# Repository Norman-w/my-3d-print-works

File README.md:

# 我的 3D 打印作品

收集自己设计、打印和验证过的 3D 打印作品。这里是后续 3D 打印模型、打印文件、预览图和说明的维护入口；原仓库保留作历史来源。

## 作品总索引

| 类别 | 项目与用途 | 项目 README | 缩略图 | 原仓库 |
|---|---|---|---|---|
| 卫浴 | 洗手盆下水管转接件：连接两种外丝、带连续过渡和梅花握持纹 | [打开](works/bathroom/sink-drain-adapter/README.md) |  | — |
| 光学 / 收纳 | 角膜塑形镜清洁套装盒：铰链、锁扣和清洁收纳结构 | [打开](works/optics/orthokeratology-lens-cleaning-kit-box/README.md) |  | [原仓库](https://github.com/Norman-w/OrthokeratologyLensCleaningKitBox) |
| 健康 / 设备保护 | 理疗仪线缆串联保护盒：保护控制板、线缆出线和散热区域 | [打开](works/health/therapy-cable-inline-box/README.md) |  | [原仓库](https://github.com/Norman-w/therapy-cable-inline-box-for-physio) |

> 收录标准：优先收录体量较小、生活中直接使用、以 3D 打印件为主体的作品。大型体育设备、复杂机构、电路和完整业务工程保留在原仓库，不进入这里。智能拖挂房车项目也保持在原仓库。

## 目录

```text
works/<作品名>/      作品源文件、打印文件、预览和验证记录
templates/work/     新作品模板
scripts/             工具脚本
```

每个作品至少记录：用途、尺寸、配套实物、`.scad` 源文件、STL / 3MF、预览图、验证结果、打印参数和未完成项。

## 状态

`concept` → `digital-verified` → `sliced` → `printed` → `assembled` → `accepted`

数字模型通过、切片成功或网页预览，都不等于实物装配验收。

## 新建作品

```sh
sh scripts/new-work.sh my-object
```

纯链接版索引：[`works/catalog.md`](works/catalog.md)

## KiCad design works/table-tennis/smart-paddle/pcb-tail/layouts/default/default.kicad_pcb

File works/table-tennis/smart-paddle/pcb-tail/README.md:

# SmartPaddle 尾部线路板（`pcb-tail`）

> 当前 **M7.C5** 组合的独立满截面尾板，与 `pcb/` 主板分开维护；充电、USB、按键和 LED 均在本板。版本只记录在说明与 KiCad 标题栏，工程、PCB、同步脚本和交接文件使用跨版本通用名称。

> **当前设计与旧板安全状态（2026-08-23）：** 当前 M7.C5 尾板为 33 个封装、502 段走线、53 个过孔和双面 GND 覆铜；KiCad DRC 为 0 error / 0 unconnected，保留 3 条已审计 warning。J1 16触点、J4/SW1、电源拓扑、主尾板线序与 M7 机械干涉门禁均通过，整机 release gate 已通过。当前达到独立工程样板下单标准；下单前仍须人工确认 Gerber/钻孔、板厚、铜厚、表面处理和颜色。所有按旧 J1 错误映射制造或已焊接的尾板及旧制造文件仍不得上电、插 USB 或再次下单。
>
> `layouts/default/export-preview/` 中除重新生成的 `fp-usb16p-selfcheck.png` 外，其余图像是本次审计前的历史预览，不是当前 J1 或制造状态的证据。

## 方向约定

| 面 | 朝向 |
|---|---|
| 正面 `F.Cu` | 拍柄末端（世界 −Y） |
| 背面 `B.Cu` | 拍头（世界 +Y） |

- `KiCad X` = 柄 `X`
- `KiCad Y` = 柄 `Z`
- 板厚沿世界 `Y`（1.0 mm）

## 专用电池接口（已放置、已布线）

- 板端：JST ACH `BM02B-ACHSS-GAN-ETF`，1.20 mm、2P、SMT 顶插；配套线端 `ACHR-02V-S` + `SACH-003G-P0.2`，成品线固定为 AWG28。
- J4 footprint：`Connector_JST:JST_ACH_BM02B-ACHSS-GAN-ETF_1x02-1MP_P1.20mm_Vertical`。电气定义固定为 **Pin 1=`BAT_P`/red**、**Pin 2=`GND`/black**；它与现有 `J2.3 BAT_P` / `J2.2 GND` 并联，电池不得接主板 `SYS_5V_IN`。
- J4 位于 B.Cu `(-2.794,-7.000) mm`、90°；Pad 1 全局 `(-0.919,-6.400) mm`，Pad 2 `(-0.919,-7.600) mm`，两个 `MP` 固定焊盘均 NC。它只沿 KiCad Y 平移 1.031 mm，为插合后的 J2 线端留出净空；当前两脚已完成布线并通过 DRC。
- 选型、采购词、电流门禁和官方资料见 [`../docs/battery-connector-jst-ach-2p/README.md`](../docs/battery-connector-jst-ach-2p/README.md)。旧 PH 方案已明确停用；官方 XH 2.50 与市售“XH2.54”不能凭名称保证互配。

## 用户按键（已换 footprint、已布线；针孔可用，推杆可选）

- SW1 已由 4.5×4.5 mm THT 换成 Omron `B3U-1000P` SMD，footprint 为 `Button_Switch_SMD:SW_SPST_B3U-1000P`；保持原锚点 `(-1.651,-5.461) mm` 和 `-90°`，没有移动或旋转其他器件。
- Pad 1=`user_btn`、Pad 2=`GND`，当前已布线并接入双面 GND 覆铜。
- 拍柄基准操作方式为 SW1 中心 Ø2.0 mm 直通针孔，可用针尖/笔尖操作，不用固定柱长期压住开关。另有从壳内装入、Ø3.0 mm 法兰防外脱的 Ø1.6 mm 可选活动推杆；推杆批量使用前仍须做行程试片。详见 [`../docs/tail-user-switch-b3u-1000p/README.md`](../docs/tail-user-switch-b3u-1000p/README.md) 和 [`../docs/tail-handle-interference/README.md`](../docs/tail-handle-interference/README.md)。当前四层制造 STL 和两张 `paddle_m7_*` 打印拼板已按正式尾板干涉事实重新生成。
- `python3 pcb-tail/scripts/audit_battery_connector_j4.py --allow-copper` 同时核对 J4 与 SW1 的位姿、针脚网络和项目内资料；铜完整性由尾板独立制造门禁另行检查。

## 主板线束接口（卧插、已布线）

- J2/J3 均为 Molex PicoBlade `53261-0471`、1.25 mm、4P、卧插 SMT；与原 53398 立插使用同一 `51021-0400` 4P 线端体系，但两种板端 footprint 不能互换。
- J2 位于 B.Cu `(-11.300,-0.600) mm`、−90°；J3 位于 B.Cu `(+6.300,-5.800) mm`、180°。两只插口均朝板内侧，线束平行 PCB 离开；逐脚网络仍以 [`ADAPTER_HARNESS.md`](ADAPTER_HARNESS.md) 为准。
- 最终紧凑布局已经由 `audit_power_architecture.py` 锁定：C1/C2 两颗同值 100 nF 分别就近服务 D1 与 U1，U3/L1/C3/C4/C6 构成已审计的本地功率岛。J2/J3/J4 的完整插合包络已写入机械干涉事实并由壳体导出链消费。
- 原厂证据、封装快照、Pin 1 方向及机械说明见 [`../docs/molex-picoblade-53261-4p-horizontal/README.md`](../docs/molex-picoblade-53261-4p-horizontal/README.md)。

## 打开

```text
pcb-tail/layouts/default/default.kicad_pro
```

## 工作流

当前尾板是已布线生产基线。J1 封装仍可重复生成和逐触点检查：

```bash
python3 pcb-tail/scripts/gen_usb_16p_vert_smt_fp.py
python3 pcb-tail/scripts/audit_usb_16p_j1.py
python3 pcb-tail/scripts/audit_battery_connector_j4.py
```

Atopile 只构建到 `layouts/staging/`；必须连续构建两次，再用项目同步脚本安全带入当前板。不得直接让 Atopile 覆盖 `layouts/default/`，`ato build` 的成功退出也不能替代逐触点审计：

```bash
cd pcb-tail
ato build
ato build
cd ..
/Applications/KiCad/KiCad.app/Contents/Frameworks/Python.framework/Versions/3.9/bin/python3 \
  pcb-tail/scripts/sync_power_architecture.py
/Applications/KiCad/KiCad.app/Contents/Frameworks/Python.framework/Versions/3.9/bin/python3 \
  pcb-tail/scripts/place_power_architecture.py
python3 scripts/validate_power_rework.py --release-gate --target tail
```

入口：`main.ato:SmartPaddleTail`（`ato.yaml`）。

外形：`web/src/data/userBezierProfiles.json` + `enclosure/parameters.scad`  
内缩：`wall_t + tail_cavity_inset`；`board_clearance = -0.50` 嵌入环槽。

壳体开孔：`./scripts/export-stl.sh`（含 Step6，按本板位姿干涉，并生成独立 B3U 活动推杆）；当前 M7.C5 已按正式尾板重新生成 `paddle_m7_*` 四层件和两张打印拼板。

## 文件

| 文件 | 说明 |
|------|------|
| `main.ato` | atopile 入口 |
| `layouts/default/default.kicad_pro` | 工程 |
| `generate_outline.py` | 从尾端截面生成 Edge.Cuts |
| `tail-outline-preview.svg` / `.png` | 2D 预览 |
| `geometry-report.txt` / `outline-facts.json` | 尺寸事实 |
| `ADAPTER_HARNESS.md` | 当前主板与本尾板的 4P→5P 转接、装配及验证 |
| `harness/adapter.json` | 由两块实际 PCB 焊盘网络校验的线束真理源 |

> 注意：本尾板为 2×4P，当前主板栈道为正反 2×5P，不能直接插接。
> 使用上述转接线束；主板的 UART TX/RX 保留为独立调试口。

## 已知瑕疵

- 当前 KiCad 3D Viewer 及导出的 3D 预览中，部分器件模型的比例/尺度与实物不一致；这只影响 3D 外观预览，不代表 PCB 焊盘、板框或器件采购尺寸发生变化。
- 3D 模型比例问题本身不用于判断焊盘；但这条说明不适用于 J1 或 J2/J3。J1 已按 H=5.8 短脚主数据表逐触点纠正；J2/J3 使用 KiCad 9 stock 53261 footprint/STEP，并另按 Molex 销售图审计 land 与 3.40 mm 配合高度。
- 下一版装配图或下单前，仍应按供应商机械图和首件实物重新检查 Type-C、卧插线束的弯曲半径、按键孔和打印公差。

## 嘉立创实验样板资料

> 已运行两板独立门禁并生成新的工程样板包；旧包仍禁止使用。尾板当前为 0 DRC error / 0 unconnected，Ø2.0 mm 针孔是独立可用的按键基准，可选推杆的试片状态不会掩盖电气验收。两板独立上传包位于 `fab/jlcpcb-orders/20260823-m7c5/`。

从仓库根目录运行：

```sh
# 仅尾板
python3 pcb/scripts/export_order_packages.py --target tail

# 主板、尾板分别形成两个独立订单包
python3 pcb/scripts/export_order_packages.py --target separate
```

当前尾板工程样板包位于 `pcb-tail/output/fab/20260817-tail-m7c5/`（本地制造输出，不纳入 Git），其中上传 ZIP 与审阅 ZIP 分离。尾板为 2 层、板厚 1.00 mm；下单页仍须人工冻结铜厚、表面处理及颜色。建议首板使用 1 oz 铜、沉金、绿色阻焊；若改用其他工艺应记录订单参数。该放行只覆盖尾板工程样板，不等于主板、整机或量产放行。

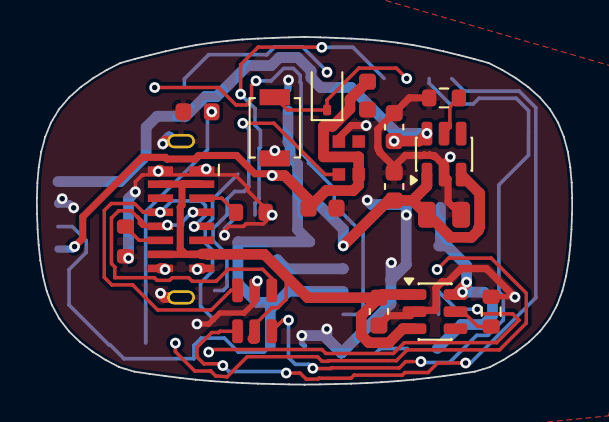
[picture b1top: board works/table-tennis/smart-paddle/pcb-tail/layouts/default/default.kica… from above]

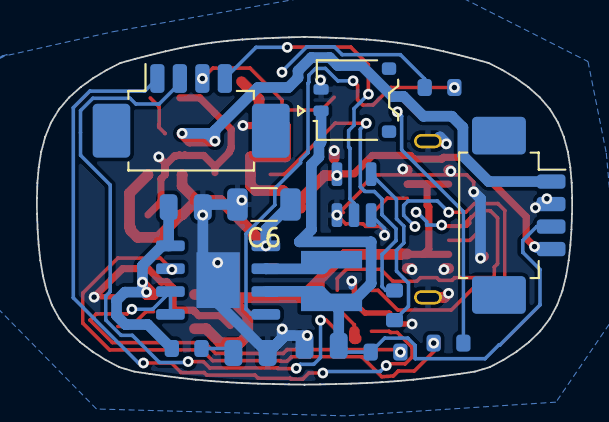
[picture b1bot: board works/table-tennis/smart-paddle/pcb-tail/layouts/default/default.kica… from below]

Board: 2 copper layers, 29.7 x 19.3 mm, 33 parts (15 on the bottom side), 26 nets.

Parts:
C1, C2: 100nF; C_0603_1608Metric
C3, C4, C5, C7: 10uF 10V X5R/X7R; C_0805_2012Metric
C6: 22uF 10V X5R/X7R; C_1206_3216Metric
C8, C9, C10: 100nF 10V X7R; C_0603_1608Metric
D1: WS2812B-2020; LED_WS2812B-2020_PLCC4_2.0x2.0mm
D2: 1N4148W; D_SOD-323
J1: USB-C-16P-VERTICAL-H5.8-SHORT; USB_C_Receptacle_16P_Vertical_SMT_Short
J2, J3: Molex 53261-0471; Molex_PicoBlade_53261-0471_1x04-1MP_P1.25mm_Horizontal
J4: BM02B-ACHSS-GAN-ETF; JST_ACH_BM02B-ACHSS-GAN-ETF_1x02-1MP_P1.20mm_Vertical
L1: XFL4020-222MEC 2.2uH; L_Coilcraft_XxL4020
LED1: LTST-C190KGKT; LED_0603_1608Metric
R1, R2: 5.1k 1%; R_0603_1608Metric
R3: 330R; R_0603_1608Metric
R4: 10k; R_0603_1608Metric
R5: 200R; R_0603_1608Metric
R6: 1k; R_0603_1608Metric
R7: 2R; R_0603_1608Metric
R8: 43.2k 1%; R_0603_1608Metric
R9: 59k 1%; R_0603_1608Metric
SW1: B3U-1000P; SW_SPST_B3U-1000P
U1: SN74AHCT1G125DBVR; SOT-23-5
U2: USBLC6-2SC6; SOT-23-6
U3: IP5305T; IP5305T_HSOP-8-1EP
U4, U5: TPS2553DBVR; SOT-23-6

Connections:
GND: C1.2, C2.2, C3.2, C4.2, C5.2, C6.2, C7.2, C8.2, C9.2, C10.2, D1.2, J1.A1, J1.A12, J1.B1, J1.B12, J1.S1, J2.2, J4.2, LED1.1, R1.2, R2.2, R8.2, R9.2, SW1.2, U1.1, U1.3, U2.2, U3.9, U4.2, U5.2
bat_p: C3.1, J2.3, J4.1, L1.2, R6.2, U3.6
cc1: J1.A5, R1.1
cc2: J1.B5, R2.1
led_ahct_y: R3.1, U1.4
led_data: J3.4, U1.2
led_din: D1.3, R3.2
led_stat_a: LED1.2, R5.2
pmic_key: R4.1, U3.5
pmic_key_isolated: D2.2, R4.2
pmic_led1: R5.1, U3.2
pmic_led23: R6.1, U3.3, U3.4
sw_node: L1.1, U3.7
system_ilim: R8.1, U4.5
usb_dn: J3.1, U2.4
usb_dn_conn: J1.A7, J1.B7, U2.3
usb_dp: J3.2, U2.6
usb_dp_conn: J1.A6, J1.B6, U2.1
user_btn: D2.1, J3.3, SW1.1
v5_sw_return: C1.1, C2.1, D1.4, J2.4, U1.5
vbus: C10.1, J1.A4, J1.A9, J1.B4, J1.B9, U2.5, U5.1, U5.3
vbus_ilim: R9.1, U5.5
vbus_limited: C4.1, R7.1, U3.1, U5.6
vin_damp_mid: C5.1, R7.2
vout_5v: C9.1, J2.1, U4.6
vout_5v_raw: C6.1, C7.1, C8.1, U3.8, U4.1, U4.3

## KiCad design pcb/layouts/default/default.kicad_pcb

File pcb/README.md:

# SmartPaddle 主板

> **当前仓库状态（2026-08-23）：** 当前硬件组合为 **M7.C5**。`layouts/default/default.kicad_pcb` 标题栏为 `SmartPaddle Main PCB / C5`。当前工作区主板为 **67 封装、1062 段线、142 个过孔、1 个 GND 铜区**（另有 MCU 天线双面规则区），KiCad 9.0.6 DRC 为 **0 error / 0 warning / 0 未连接**，`scripts/validate_power_rework.py --release-gate --target all` 已通过。当前板已达到**工程样板下单**标准，但仍不是量产放行。最新独立下单包见 `fab/jlcpcb-orders/20260823-m7c5/`；不要使用历史 C4 包。现行布线与放行说明见 [`ROUTING_HANDOFF.md`](ROUTING_HANDOFF.md) 和 [`../docs/power-architecture-rework/README.md`](../docs/power-architecture-rework/README.md)。
>
> **实物与源文件必须区分：** 已回板的旧 C4（SHA256 `86389d…`）仍可作为历史 bring-up 对象，但它不再等于当前 KiCad 源板；旧装配图、Gerber 与制造就绪结论不得套用到当前 67 件重整版。

## 当前 C5 布线入口

电气真理源仍是通用文件 `main.ato`，当前 PCB 仍是通用路径 `layouts/default/default.kicad_pcb`；版本号只记录在说明和 KiCad 标题栏，不另建 `C5_*` PCB、同步脚本或快照入口。开始布线前运行：

```sh
python3 scripts/validate_power_rework.py
```

门禁无铜交接基线为主板 67 件、尾板 33 件。现板已有铜，默认 `validate_power_rework.py` 会因非 0 铜失败；语义审计用 `audit_power_architecture.py --allow-copper`。用户完成布线和铺地后，再运行 `python3 scripts/validate_power_rework.py --release-gate`；在 0 未连接和全部跨层审计通过以前不会放行制造导出。

当前 `SW_BOOT`、`SW_EN`、`SW_PWR` 是与尾板同系列的 Omron `B3U-1000P` SMD 开关，均标记 DNP，只供裸板测试选择性手焊，正式外壳不开孔。ESP32-S3 footprint 内的 `ESP32_ANTENNA_HOST_KEEP_OUT` 同时禁止 F/B 面走线、过孔、焊盘、铺铜和其它封装；布线时不得删除或绕过。机械参数和预览见 [`../docs/mechanical-handoff/README.md`](../docs/mechanical-handoff/README.md)。

## 历史 C4 PCB 生成管线（归档）

以下 Step 1–4、63 件快照和 C4 制造说明只解释已回板 C4 的生成历史；它们不是当前 C5 的同步或布线入口。

管线的机械基准来自 `enclosure/paddle_shell.scad` 的 `rigid_pcb_slot_points`（V3 起尾端平收，无金手指窄尖）。
每一步都是独立的 Python 脚本，按顺序执行：

| Step | 脚本 | 功能 | 操作层 |
| --- | --- | --- | --- |
| 1 | `scripts/step1_clear_and_reference.py` | 清空全部元素，绘制 SCAD 参考轮廓、坐标十字、PZT 腔体圆、X±/Y± 方向标记 | `Dwgs.User` |
| 2 | `scripts/step2_substrate_outline.py` | 清空 `Edge.Cuts`，绘制 PCB 基材外形（内缩 0.30mm、PZT 码头缩回、拍柄截断） | `Edge.Cuts` |
| 3 | `scripts/step3_module_cutouts.py` | 刷新 ESP32-S3 和 IMU 模块矩形开孔，并生成嵌入焊接 rule area | `Edge.Cuts` + rule area |
| 3.1 | `ato build`（由根目录入口调用） | 用 `ato.yaml` 锁定的 0.12.5 生成最新 C4 网表 | 构建输出 |
| 3.2 | `scripts/step3_import_netlist.py` + `scripts/step3_finalize_generated_board.py` | 拒绝旧/C3/拓扑不符网表，通过 63 地址全量门禁后同步受审 C4 网络；无摆放地恢复可读元数据和背面尾插几何 | 网络 + 元数据 |
| C3→C4 | `scripts/migrate_c3_to_c4_unrouted.py` | 换 S3、加入比较器/DAC/去耦/ADC DNP，并按受审表赋网；显式清除 C3 铜线 | 封装 + 网络 + 铜线 |
| 4 | `scripts/step4_ato_placement.py` | 从 snapshot 恢复大陆/宽栈道/PZT/尾插并放置 C4 新器件；存在全板 C4 快照时最后优先恢复其 63 个变换 | 封装 |

> ~~step4.4 金手指加强小板~~ 已废弃：尾插改为 MX1.25 正反 5P，不再生成 `TAIL_STIFF_*` / `TAIL_FINGER_*`。

Step1 是破坏性的（清空后重新开始），Step2~4 仅修改各自负责的层。

### 运行方式

```sh
KPY=/Applications/KiCad/KiCad.app/Contents/Frameworks/Python.framework/Versions/3.9/bin/python3
PCB=pcb/layouts/default/default.kicad_pcb

# 完整重建（从零开始，丢弃原有封装）:
$KPY pcb/scripts/step1_clear_and_reference.py
$KPY pcb/scripts/step2_substrate_outline.py
$KPY pcb/scripts/step3_module_cutouts.py
# atopile build 生成封装（须使用 ato.yaml 锁定的 0.12.5）...
$KPY pcb/scripts/step4_ato_placement.py --force
# 若 ato 未带上 Molex 尾插封装，再补：
# $KPY pcb/scripts/apply_tail_mx125.py
```

### 位置快照（step1 前备份 / step4 自动吃）

| 区域 | 备份 | 快照文件 |
| --- | --- | --- |
| PZT 岛 | `step4.1_backup_docks.py` | `dock_snapshot.json` |
| 大陆阻容 | `step4.1b_backup_mainland.py` | `mainland_snapshot.json` |
| 宽栈道三键 | `step4.1c_backup_corridor.py` | `corridor_snapshot.json` |
| 尾插 F/B | `step4.1d_backup_tail.py` | `tail_snapshot.json` |
| C4 全部 63 器件（最终真理源） | 菜单 Step 4.1e / `step4.1e_backup_c4_placement.py` | `c4_placement_snapshot.json` |

### 部分更新（保留封装）

```sh
# 仅重绘机械层，不影响已有封装:
$KPY pcb/scripts/step1_clear_and_reference.py   # 清机械层+重绘参考线
$KPY pcb/scripts/step2_substrate_outline.py      # 重绘基材外形
$KPY pcb/scripts/step3_module_cutouts.py         # 重绘模块开孔和 IMU rule area
$KPY pcb/scripts/step4_ato_placement.py          # 仅移动仍位于 ato 网格位置的封装
```

### 历史 C4 手工布线板

当前 `layouts/default/default.kicad_pcb` 的手工布线/铺铜已于提交 `828f6e1` 回存；KiCad 9.0.6 DRC 为 0 未连接、0 error，剩余 72 项均为已复核的丝印/库封装一致性 warning。原交接板的独立 `TP_GND` 已按 Norman 确认取消；2026-07-30 的 atopile 0.12.5 新网表、当前板和全板快照均为 63 个封装。最终物理焊盘对网、Gerber/钻孔/ZIP 试导出和装配包已通过；裸板可投工程样板，但整机仍有电源、热、USB、内部 PTH 锣槽和回板实测条件，见 [`C4_FAB_READINESS.md`](C4_FAB_READINESS.md)。不得再运行 Step 3.2 写入或带 `--yes-clear-copper` 的迁移命令。

```sh
# 校验器名称保留历史的 unrouted；当前有铜板只能先使用其显式 check-only/允许铜线模式。
# 未确认参数前不要直接运行默认写入或“要求无铜线”的模式。
$KPY pcb/scripts/validate_c4_unrouted_board.py --help
```

迁移脚本不替代 atopile 编译器。仓库 `ato.yaml` 自 2026-06-13 起锁定 `0.12.5`；提交 `c9df0aa` 写明“适配 atopile 0.12.5”，`f10342b` 写明“ato build 刷新”。这些是强版本意图证据，但没有 C3 出板时的运行日志/工具指纹能证明当时实际可执行文件版本。C4 于 2026-07-30 从标准路径 `~/.local/share/uv/tools/atopile/bin/ato` 实测版本 0.12.5，并由项目 Step 3.1 明确 `Build successful`；旧 `~/.atopile-env` 的 0.2.69 未参与生成。新 `.net` 为 63 个 C4 地址，旧 48 地址 C3 `.net` 仍只作历史产物。

Step 3.2 先核对 S3 的 ato/封装/固件/导入器脚位，再递归定位实际嵌套的 `default.net`，拒绝早于 `ato.yaml` / `main.ato` / `parts.ato` / S3 pinmap 的网表，解析仓库真实的多行 `atopile_address` / node 格式，并验证 63 个地址、182 个已连接焊盘号以及完整拆网/并网关系。只有无 track/via、无铜区交接板才允许写入；重复同号焊盘的 188 个物理实例会全部赋网。随后元数据收尾器恢复 63 个可读 Reference/Value、四个 DNP、IMU 3D 缩放及 Atopile 0.12.5 会翻错的背面尾插内部几何，并断言 0 个元件坐标/角度/板层变化。若 Norman 已开始布线，只运行 pinmap 校验与 `--check-only`，不得让 Step 3.2 改写板文件。

### 截图验证

```sh
kicad-cli pcb render --side top --width 1600 --height 1200 --background opaque --quality high \
  -o pcb/output/stepN_top.png pcb/layouts/default/default.kicad_pcb
```

### 器件布局分区

| 区域 | 内容 | 列数 |
| --- | --- | --- |
| MCU X+ | 电源锁存电路 + LED 接口（Q×2、D×1、R×3、LDO×1、C×2） | 2 |
| MCU X- | 调试焊盘 *仅此*（GND、VCC、VBAT、UART_TX、UART_RX） | 1 |
| IMU X- | LDO 滤波电容（c_in、c_out） | 1 |
| IMU X+ | 剩余调试焊盘（EN、BOOT、PWR_LATCH、IMU_KEY、IMU_GPIO、VBUS、LED_DATA） | 2 |

### 电气逻辑

电气连接定义在 `main.ato`，`ato.yaml` 指向 `main.ato:SmartPaddleRigid`。

项目自 2026-06-15 起的一键入口是根目录 `scripts/scad_to_kicad.sh`，不是已删除的旧 `generate_kicad.py`。只做电气生成时，从仓库根目录运行它并选择 **Step 3.1**；随后选择 **Step 3.2** 导入新网表。脚本会打印实际可执行文件和版本，在不是 `0.12.5` 时拒绝生成，并要求构建日志出现 `Build successful`，避免 Atopile 报错却返回零时误报完成。Step 3.2 不做元件摆放。C4 不要选择全链路 `a`、Step 4 或任何 Step 5 路由操作。

```sh
./scripts/scad_to_kicad.sh
# 选择 3.1；成功后继续选择 3.2
```

标准脚本默认使用 `~/.local/share/uv/tools/atopile/bin/ato`，可由调用者已有的 `ATO=/绝对路径/ato` 配置覆盖；仓库脚本不会安装、升级或重建 Python/atopile 环境。

封装以 `atopile_address` 属性作为电气真源实例。

管线脚本不处理布线，KiCad 仍负责:

- 元件放置决策
- 所有走线、过孔、敷铜和 DRC 清理
- 最终原理图图形维护

### 嵌入式 IMU 半孔接口

`layouts/lib/footprints.pretty/IM948_CUTOUT.kicad_mod` 将 IM948 建模为内嵌模块接口:

- IMU 模块本体进入 `step3_module_cutouts.py` 生成的内部开孔，不与主 PCB 厚度方向叠放。
- 16 个 IMU 引脚使用 PTH 圆孔焊盘；开孔边线切过这些焊盘，形成主 PCB 侧的半孔/邮票孔焊接界面。
- KiCad 电气上仍把 `IMU_IM948` 当作普通元件，所以可以直接从这些焊盘往主板引线。
- `layouts/default/default.kicad_dru` 用 `IMU_EMBEDDED_CASTELLATED_EDGE` rule area 仅在 IMU 嵌入接口附近放宽 `edge_clearance`；普通板边仍按 0.5mm 检查。
- `layouts/default/default.kicad_pro` 的工程级 `min_copper_edge_clearance` 保持为 0mm，这是为了允许 custom rule 对 IMU 区域设置负的 edge clearance。不要删除 `.kicad_dru`，否则普通板边的 0.5mm 规则不会被恢复。

## 历史 C4 状态

仓库历史仍包含 C4 手工布线/铺铜快照、63 件全板快照和最终制造审计；当前 C5 已完成新的布线/铺铜并有独立放行门禁，不能用下列历史结果替代现行 C5 包。C4 历史后续工作记录：

- 当前 `c4_placement_snapshot.json` 已经 Step 4.1e 只读复核；禁止无意使用 `--replace` 覆盖接受基线
- 嘉立创每次打板（裸板 / 部分 SMT）的通用操作见 [`JLCPCB_ORDERING.md`](JLCPCB_ORDERING.md)；下单时重新运行 `export_jlcpcb.py`（需要贴片时加 `--smt`），不得复用临时审计 ZIP
- 按 [`C4_FAB_READINESS.md`](C4_FAB_READINESS.md) 完成小批量回板 bring-up；未通过外置 5 V、AP2112 热、USB、PZT、射频和槽边焊接前不得转量产
- 尾板壳体：[`../enclosure/README.md`](../enclosure/README.md) + [`../pcb-tail/`](../pcb-tail/)；规划见 [`C5_PLAN.md`](C5_PLAN.md)。旧主板延长/中间开窗预览已废弃

历史 C4 最终可打印装配包曾生成到本地 `output/pdf/smartpaddle-ai-assembly/`：14 页 A4，63 个封装各映射一次，顶/底面、Pad 1、DNP、安装顺序、检查单和 BOM 均已渲染复核。`output/pdf/assembly-package/` 16 页文件是更早的摆放前快照；二者都只能作历史资料，不能用于当前 C5。尾插历史 HTML/端面图位于 `output/assembly/`。

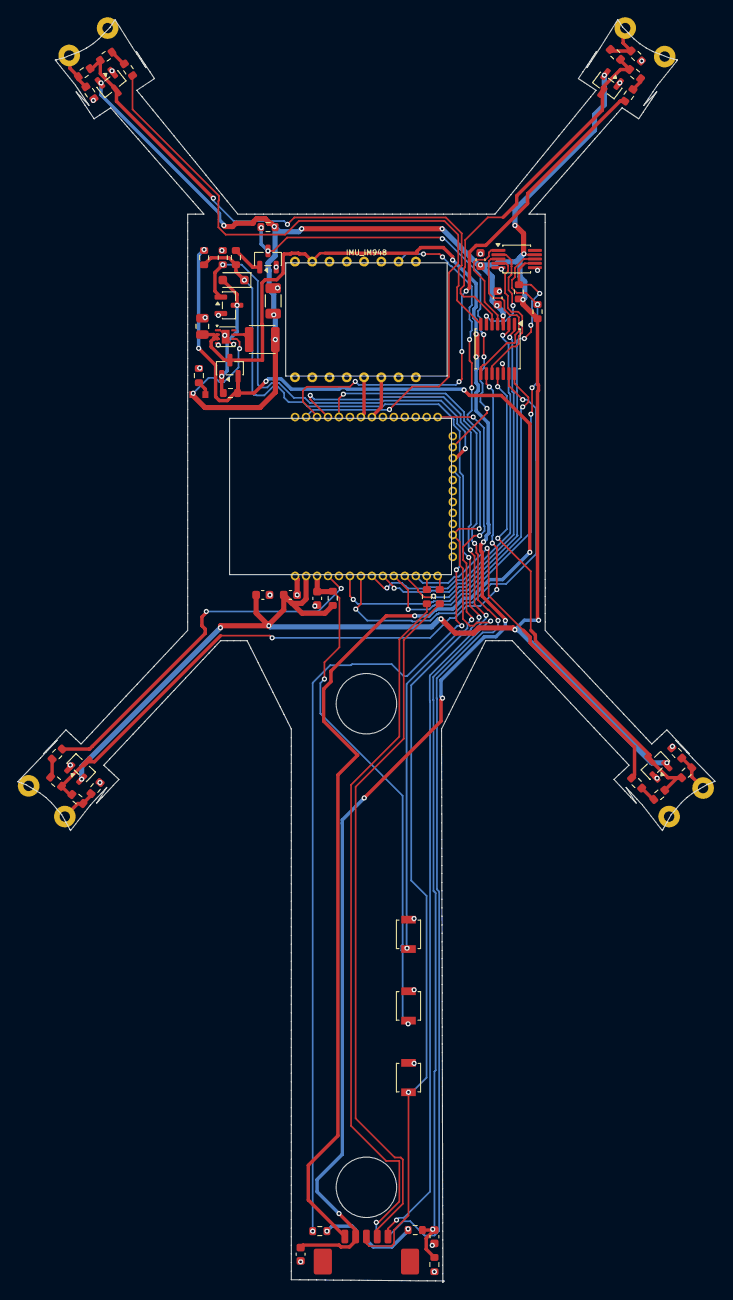
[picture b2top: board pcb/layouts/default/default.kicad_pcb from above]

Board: 2 copper layers, 80.8 x 146.2 mm, 67 parts (1 on the bottom side), 51 nets.

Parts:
BAT_C_ADC_100N: 100nF; C_0603_1608Metric
BAT_R_BOT_1M: 1M; R_0603_1608Metric
BAT_R_TOP_1M: 1M; R_0603_1608Metric
D_BTN_START: 1N4148W; D_SOD-323_HandSoldering
IMU_IM948: IM948; IM948_CUTOUT
JP_ADC_BL: 0R DNP; R_0603_1608Metric
JP_ADC_BR: 0R DNP; R_0603_1608Metric
JP_ADC_TL: 0R DNP; R_0603_1608Metric
JP_ADC_TR: 0R DNP; R_0603_1608Metric
LED_C_SUP_100N: 100nF; C_0603_1608Metric
LED_MCU_PWR: 0603 power; LED_0603
LED_R_DATA_330R: 330R; R_0603_1608Metric
MCU_C_BULK_10U: 10uF 6.3V X5R/X7R; C_0603_1608Metric
MCU_C_DEC_100N: 100nF 10V X7R; C_0603_1608Metric
MCU_C_EN_1U: 1uF 10V X5R/X7R; C_0603_1608Metric
MCU_ESP32_S3: ESP32-S3-WROOM-1-N16R8; ESP32-S3-WROOM-1_CUTOUT
PW_BUCK_3V3: TPS62162DSGR; Texas_DSG0008A_WSON-8-1EP_2x2mm_P0.5mm_EP0.9x1.6mm
PW_C_IN_10U: 10uF 10V X5R/X7R; C_0805_2012Metric
PW_C_OUT_22U: 22uF 6.3V X5R/X7R; C_1206_3216Metric
PW_L_BUCK_2U2: XFL3012-222MEC 2.2uH; L_Coilcraft_XFL3012
PW_Q_BTN_SENSE: AO3400A; SOT-23
PW_Q_LATCH: AO3400A; SOT-23
PW_Q_LOAD: AO3401A; SOT-23
PW_R_BTN_GPIO_PU_100K: 100k 1%; R_0603_1608Metric
PW_R_BTN_RAW_PU_100K: 100k 1%; R_0603_1608Metric
PW_R_BTN_SER_1K: 1k; R_0603_1608Metric
PW_R_EN_PU_10K: 10k; R_0603_1608Metric
PW_R_GATE_100K: 100k; R_0603_1608Metric
PW_R_LATCH_PD_100K: 100k; R_0603_1608Metric
PZT_BL_D_CLAMP: BAT54S; SOT-23
PZT_BL_GND: PZT GND wire; PZT_WirePad_THT_D2.5mm_Drill1.2mm
PZT_BL_R_DIS_1M: 1M; R_0603_1608Metric
PZT_BL_R_SER_4K7: 4.7k; R_0603_1608Metric
PZT_BL_SIG: PZT signal wire; PZT_WirePad_THT_D2.5mm_Drill1.2mm
PZT_BR_D_CLAMP: BAT54S; SOT-23
PZT_BR_GND: PZT GND wire; PZT_WirePad_THT_D2.5mm_Drill1.2mm
PZT_BR_R_DIS_1M: 1M; R_0603_1608Metric
PZT_BR_R_SER_4K7: 4.7k; R_0603_1608Metric
PZT_BR_SIG: PZT signal wire; PZT_WirePad_THT_D2.5mm_Drill1.2mm
PZT_CMP_TLV9034: TLV9034PWR; TSSOP-14_4.4x5mm_P0.65mm
PZT_C_CMP_100N: 100nF; C_0603_1608Metric
PZT_C_DAC_100N: 100nF; C_0603_1608Metric
PZT_DAC_MCP4728: MCP4728-E/UN; MSOP-10_3x3mm_P0.5mm
PZT_R_ADC_BL_1M: 1M; R_0603_1608Metric
PZT_R_ADC_BR_1M: 1M; R_0603_1608Metric
PZT_R_ADC_TL_1M: 1M; R_0603_1608Metric
PZT_R_ADC_TR_1M: 1M; R_0603_1608Metric
PZT_R_SCL_PU_4K7: 4.7k; R_0603_1608Metric
PZT_R_SDA_PU_4K7: 4.7k; R_0603_1608Metric
PZT_TL_D_CLAMP: BAT54S; SOT-23
PZT_TL_GND: PZT GND wire; PZT_WirePad_THT_D2.5mm_Drill1.2mm
PZT_TL_R_DIS_1M: 1M; R_0603_1608Metric
PZT_TL_R_SER_4K7: 4.7k; R_0603_1608Metric
PZT_TL_SIG: PZT signal wire; PZT_WirePad_THT_D2.5mm_Drill1.2mm
PZT_TR_D_CLAMP: BAT54S; SOT-23
PZT_TR_GND: PZT GND wire; PZT_WirePad_THT_D2.5mm_Drill1.2mm
PZT_TR_R_DIS_1M: 1M; R_0603_1608Metric
PZT_TR_R_SER_4K7: 4.7k; R_0603_1608Metric
PZT_TR_SIG: PZT signal wire; PZT_WirePad_THT_D2.5mm_Drill1.2mm
R_MCU_PWR_1K: 1k; R_0603_1608Metric
SW_BOOT: B3U-1000P DNP; SW_SPST_B3U-1000P
SW_EN: B3U-1000P DNP; SW_SPST_B3U-1000P
SW_PWR: B3U-1000P DNP; SW_SPST_B3U-1000P
TAIL_MX125_B, TAIL_MX125_F: MX1.25-5P; Molex_PicoBlade_53261-0571_1x05-1MP_P1.25mm_Horizontal
USB_R_DN_22R: 22R 1%; R_0603_1608Metric
USB_R_DP_22R: 22R 1%; R_0603_1608Metric

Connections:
bat_cell_p: BAT_R_TOP_1M.1, TAIL_MX125_B.3
bat_sense: BAT_C_ADC_100N.1, BAT_R_BOT_1M.1, BAT_R_TOP_1M.2, IMU_IM948.7, MCU_ESP32_S3.17
boot_btn: MCU_ESP32_S3.27, SW_BOOT.1
btn_sw: D_BTN_START.1, PW_R_BTN_RAW_PU_100K.1, PW_R_BTN_SER_1K.1, SW_PWR.1, TAIL_MX125_F.3
buck_sw: PW_BUCK_3V3.7, PW_L_BUCK_2U2.1
button_sense_gate: PW_Q_BTN_SENSE.1, PW_R_BTN_SER_1K.2
c: LED_MCU_PWR.2, R_MCU_PWR_1K.1
en: MCU_C_EN_1U.1, MCU_ESP32_S3.3, PW_R_EN_PU_10K.1, SW_EN.1
gnd: BAT_C_ADC_100N.2, BAT_R_BOT_1M.2, IMU_IM948.1, IMU_IM948.8, IMU_IM948.16, LED_C_SUP_100N.2, MCU_C_BULK_10U.2, MCU_C_DEC_100N.2, MCU_C_EN_1U.2, MCU_ESP32_S3.1, MCU_ESP32_S3.40, PW_BUCK_3V3.1, PW_BUCK_3V3.4, PW_BUCK_3V3.5, PW_BUCK_3V3.9, PW_C_IN_10U.2, PW_C_OUT_22U.2, PW_Q_BTN_SENSE.2, PW_Q_LATCH.2, PW_R_LATCH_PD_100K.2, PZT_BL_D_CLAMP.1, PZT_BL_GND.1, PZT_BL_R_DIS_1M.2, PZT_BR_D_CLAMP.1, PZT_BR_GND.1, PZT_BR_R_DIS_1M.2, PZT_CMP_TLV9034.12, PZT_C_CMP_100N.2, PZT_C_DAC_100N.2, PZT_DAC_MCP4728.5, PZT_DAC_MCP4728.6, PZT_TL_D_CLAMP.1, PZT_TL_GND.1, PZT_TL_R_DIS_1M.2, PZT_TR_D_CLAMP.1, PZT_TR_GND.1, PZT_TR_R_DIS_1M.2, R_MCU_PWR_1K.2, SW_BOOT.2, SW_EN.2, SW_PWR.2, TAIL_MX125_B.5
i2c_scl: MCU_ESP32_S3.11, PZT_DAC_MCP4728.7, PZT_R_SCL_PU_4K7.2
i2c_sda: MCU_ESP32_S3.10, PZT_DAC_MCP4728.8, PZT_R_SDA_PU_4K7.2
imu_uart_rx: IMU_IM948.14, MCU_ESP32_S3.33
imu_uart_tx: IMU_IM948.13, MCU_ESP32_S3.34
led_data: LED_R_DATA_330R.1, MCU_ESP32_S3.23
led_din: LED_R_DATA_330R.2, TAIL_MX125_B.4
p_gate: D_BTN_START.2, PW_Q_LATCH.3, PW_Q_LOAD.1, PW_R_GATE_100K.1
pwr_latch: MCU_ESP32_S3.24, PW_Q_LATCH.1, PW_R_LATCH_PD_100K.1
pzt_adc_bl: JP_ADC_BL.2, MCU_ESP32_S3.4
pzt_adc_br: JP_ADC_BR.2, MCU_ESP32_S3.12
pzt_adc_iso_bl: JP_ADC_BL.1, PZT_R_ADC_BL_1M.2
pzt_adc_iso_br: JP_ADC_BR.1, PZT_R_ADC_BR_1M.2
pzt_adc_iso_tl: JP_ADC_TL.1, PZT_R_ADC_TL_1M.2
pzt_adc_iso_tr: JP_ADC_TR.1, PZT_R_ADC_TR_1M.2
pzt_adc_tl: JP_ADC_TL.2, MCU_ESP32_S3.39
pzt_adc_tr: JP_ADC_TR.2, MCU_ESP32_S3.38
pzt_cmp_in_bl: PZT_BL_D_CLAMP.3, PZT_BL_R_SER_4K7.2, PZT_CMP_TLV9034.9, PZT_R_ADC_BL_1M.1
pzt_cmp_in_br: PZT_BR_D_CLAMP.3, PZT_BR_R_SER_4K7.2, PZT_CMP_TLV9034.11, PZT_R_ADC_BR_1M.1
pzt_cmp_in_tl: PZT_CMP_TLV9034.7, PZT_R_ADC_TL_1M.1, PZT_TL_D_CLAMP.3, PZT_TL_R_SER_4K7.2
pzt_cmp_in_tr: PZT_CMP_TLV9034.5, PZT_R_ADC_TR_1M.1, PZT_TR_D_CLAMP.3, PZT_TR_R_SER_4K7.2
pzt_edge_bl: MCU_ESP32_S3.6, PZT_CMP_TLV9034.14
pzt_edge_br: MCU_ESP32_S3.7, PZT_CMP_TLV9034.13
pzt_edge_tl: MCU_ESP32_S3.9, PZT_CMP_TLV9034.1
pzt_edge_tr: MCU_ESP32_S3.8, PZT_CMP_TLV9034.2
pzt_raw_bl: PZT_BL_R_DIS_1M.1, PZT_BL_R_SER_4K7.1, PZT_BL_SIG.1
pzt_raw_br: PZT_BR_R_DIS_1M.1, PZT_BR_R_SER_4K7.1, PZT_BR_SIG.1
pzt_raw_tl: PZT_TL_R_DIS_1M.1, PZT_TL_R_SER_4K7.1, PZT_TL_SIG.1
pzt_raw_tr: PZT_TR_R_DIS_1M.1, PZT_TR_R_SER_4K7.1, PZT_TR_SIG.1
pzt_vref_bl: PZT_CMP_TLV9034.8, PZT_DAC_MCP4728.3
pzt_vref_br: PZT_CMP_TLV9034.10, PZT_DAC_MCP4728.4
pzt_vref_tl: PZT_CMP_TLV9034.6, PZT_DAC_MCP4728.2
pzt_vref_tr: PZT_CMP_TLV9034.4, PZT_DAC_MCP4728.1
sys_5v_in: PW_Q_LOAD.2, PW_R_BTN_RAW_PU_100K.2, PW_R_GATE_100K.2, TAIL_MX125_F.1
sys_5v_sw: IMU_IM948.2, LED_C_SUP_100N.1, PW_BUCK_3V3.2, PW_BUCK_3V3.3, PW_C_IN_10U.1, PW_Q_LOAD.3, TAIL_MX125_F.2
uart_rx: MCU_ESP32_S3.36, TAIL_MX125_B.1
uart_tx: MCU_ESP32_S3.37, TAIL_MX125_F.5
usb_dn: MCU_ESP32_S3.13, USB_R_DN_22R.2
usb_dn_conn: TAIL_MX125_B.2, USB_R_DN_22R.1
usb_dp: MCU_ESP32_S3.14, USB_R_DP_22R.2
usb_dp_conn: TAIL_MX125_F.4, USB_R_DP_22R.1
user_btn: MCU_ESP32_S3.25, PW_Q_BTN_SENSE.3, PW_R_BTN_GPIO_PU_100K.1
vcc: LED_MCU_PWR.1, MCU_C_BULK_10U.1, MCU_C_DEC_100N.1, MCU_ESP32_S3.2, PW_BUCK_3V3.6, PW_C_OUT_22U.1, PW_L_BUCK_2U2.2, PW_R_BTN_GPIO_PU_100K.2, PW_R_EN_PU_10K.2, PZT_BL_D_CLAMP.2, PZT_BR_D_CLAMP.2, PZT_CMP_TLV9034.3, PZT_C_CMP_100N.1, PZT_C_DAC_100N.1, PZT_DAC_MCP4728.9, PZT_R_SCL_PU_4K7.1, PZT_R_SDA_PU_4K7.1, PZT_TL_D_CLAMP.2, PZT_TR_D_CLAMP.2

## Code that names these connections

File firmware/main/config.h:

#pragma once
#include <cstdint>

#include "driver/gpio.h"
#include "driver/uart.h"

// --- C4 ESP32-S3-WROOM-1-N16R8 pin map ---
// Truth source: pcb/lib/esp32s3wroom1/pinmap.py (top view, antenna -X).
// GPIO35..37 are reserved by octal PSRAM. GPIO0/3/45/46 are straps; only
// GPIO0 is used, exclusively for the BOOT switch.

// --- Piezo comparator edges (TLV9034 push-pull outputs) ---
#define PIEZO_PIN_1 GPIO_NUM_16  // Top-left; TLV9034 channel 2
#define PIEZO_PIN_2 GPIO_NUM_15  // Top-right; TLV9034 channel 1
#define PIEZO_PIN_3 GPIO_NUM_6   // Bottom-left blade corner
#define PIEZO_PIN_4 GPIO_NUM_7   // Bottom-right blade corner

// Optional high-impedance ADC peeks. Fit the matching JP_ADC_* 0R and set
// PZT_ADC_PEEK_ENABLE=1 for diagnostics; leave all jumpers DNP in production.
#define PZT_ADC_PIN_1 GPIO_NUM_1
#define PZT_ADC_PIN_2 GPIO_NUM_2
#define PZT_ADC_PIN_3 GPIO_NUM_4
#define PZT_ADC_PIN_4 GPIO_NUM_8
#define PZT_ADC_PEEK_ENABLE 0

// MCP4728 programmable thresholds (internal 2.048V reference, gain x1).
#define PZT_I2C_SDA GPIO_NUM_17
#define PZT_I2C_SCL GPIO_NUM_18
#define PZT_DAC_I2C_ADDRESS 0x60
#define PZT_THRESHOLD_MV_TL 220
#define PZT_THRESHOLD_MV_TR 220
#define PZT_THRESHOLD_MV_BL 220
#define PZT_THRESHOLD_MV_BR 220

// --- IMU pins (IM948, UART1) ---
#define IMU_UART_NUM   UART_NUM_1
#define IMU_UART_TX    GPIO_NUM_41  // pad 34 → IMU RXD
#define IMU_UART_RX    GPIO_NUM_40  // pad 33 ← IMU TXD
#define IMU_UART_BAUD  115200       // 固定 115200（升 230400 会在软复位后错位）
#define IMU_UART_BAUD_HIGH 230400   // 保留常量；当前固件不再自动升级
// 诊断：1=跳过 init_imu / imu_task；确认后改回 0
#define SKIP_IMU_INIT  0
// 诊断：串口打印 IMU 姿态（0=关；1=开）。IMU 未修好前保持关闭，避免刷屏；PZT 敲击日志不受影响
#define IMU_UART_LOG_ENABLE 0
// 开启后的打印频率（Hz）；仅当 IMU_UART_LOG_ENABLE=1 时生效
#define IMU_UART_REPORT_HZ  5

// --- WiFi defaults (override via WebSocket config later) ---
#define WIFI_SSID_DEFAULT   "SmartPaddle"
#define WIFI_PASS_DEFAULT   "paddle123"

// --- WebSocket server ---
#define WS_SERVER_HOST      "192.168.4.1"  // Default: phone hotspot or local server
#define WS_SERVER_PORT      8000
#define WS_PATH             "/ws/paddle"

// --- IM948 Timing ---
#define IMU_REPORT_HZ       100    // 115200 + 精简订阅；TAG_ALL@250 需 230400
#define IMU_RX_BUF_SIZE     4096   // UART 接收缓冲区

// --- Ring buffer ---
#define RING_BUF_SIZE       65536  // 通用环缓冲区

// --- LED ---
#define LED_PIN GPIO_NUM_21  // WS2812C RGB LED

// Battery divider (BAT_CELL_P / 2) is also wired to IM948 ADIN.
#define BAT_SENSE_GPIO GPIO_NUM_9

// --- 电源自锁 + 唯一用户键 SW_PWR（ESP32-S3-WROOM-1）---
// pad 24 = GPIO47 → PWR_LATCH（高电平保持开机）
// pad 25 = GPIO48 → 独立 NMOS 隔离后的 SW_PWR 读回（按下为高）
// 产品只暴露 SW_PWR：长按关机；短按后再长按 → 恢复出厂（见 power_control）
// SW_BOOT(GPIO0/pad27) 与 SW_EN 仅维护烧录/复位，固件不监测
#define PWR_LATCH_GPIO              GPIO_NUM_47
#define USER_BTN_GPIO               GPIO_NUM_48
#define USER_BTN_ACTIVE_LEVEL       1
#define POWER_OFF_HOLD_MS           2000
#define FACTORY_RESET_SHORT_MAX_MS  500
#define FACTORY_RESET_HOLD_MS       10000
#define FACTORY_RESET_COMBO_WINDOW_MS 3000

#define BOOT_BTN_GPIO        GPIO_NUM_0  // 硬件下载模式脚；勿当用户键

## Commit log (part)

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2026-06-11 🔧 修正 FPC 模块槽位与 USB 走线
2026-06-11 📦 提交 KiCad 封装库与板文件记录
2026-06-11 🧹 删除本地 workspace 配置
2026-06-11 🛠️ 修复 KiCad 硬错误与地平面填充
2026-06-11 ✅ 清理 KiCad DRC 剩余问题
2026-06-11 🧹 忽略 KiCad MCP 验证产物
2026-06-11 🔧 修正 PZT 调理焊盘朝向
2026-06-11 🔧 按槽方向分布 PZT 调理器件
2026-06-11 🔧 旋转 PZT 调理图形框
2026-06-11 🔧 调整 PZT 槽向辅助框
2026-06-11 🔧 增加拍柄焊接尾巴
2026-06-11 🧪 建立刚性PCB研究版
2026-06-11 🧩 改为骨架PCB与模块开窗
2026-06-12 🧭 重置刚性PCB机械基准
2026-06-12 🧭 统一刚性PCB参考坐标
2026-06-12 🧭 对齐PCB码头到SCAD参考槽
2026-06-12 🧠画参考线和裁切板子
2026-06-12 🔌 完善刚性PCB atopile 连接逻辑
2026-06-13 📦 修正模块邮票孔封装和3D模型
2026-06-13 📐 修正IM948邮票孔偏置和模型尺度
2026-06-14 🛠️ 修正刚性PCB机械参考与元件预摆
2026-06-22 📌 记录码头元件与局部走线人工调整
2026-06-22 🧭 修复码头快照恢复并还原双面金手指
2026-06-22 📐 按金手指相对定位测试焊盘
2026-06-30 💾 备份手工码头走线现场
2026-06-30 🔌 脚本化 PZT 换层与背面地铜
